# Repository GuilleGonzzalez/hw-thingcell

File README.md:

# ThingCell

## Description
'ThhingCell' is a device designed to control a other devices with a relay with MQTT over 4G .

Firmware used in this device is [fw-thingcell](https://github.com/GuilleGonzzalez/fw-thigcell), a custom made firmware implemented using [Arduino Home Assistant](https://github.com/dawidchyrzynski/arduino-home-assistant/tree/main) Arduino library ([docs](https://dawidchyrzynski.github.io/arduino-home-assistant/)).

## Power supply (WIP)

## Microprocessor (WIP)
Espressif [ESP8266](https://www.espressif.com/en/products/modules) module.

## Environmental sensing (WIP)
The board has enviromental sensors to measure temperature, humidity and atmospheric pressure:

### Temperature and humidity sensor
* Sensirion [SHT40](https://sensirion.com/products/catalog/SHT40).

### Pressure sensor
* Bosch [BMP581](https://www.bosch-sensortec.com/products/environmental-sensors/pressure-sensors/bmp581/).
  
## LEDs and buttons (WIP)

## Pin assignment (WIP)

| PIN     | Func    |
| ------- | ------- |
| GPIOx   | F1    |

## Enclosure (WIP)
* Custom made in [Fusion 360](https://www.autodesk.es/products/fusion-360/overview).

# Changelog (WIP)
All notable changes to this project will be documented in this section.

The format is based on [Keep a Changelog](https://keepachangelog.com/en/1.0.0/)

## [unreleased] - 2023-09-06
Unreleased

[Unreleased]: https://github.com/GuilleGonzzalez/hw-thingcell

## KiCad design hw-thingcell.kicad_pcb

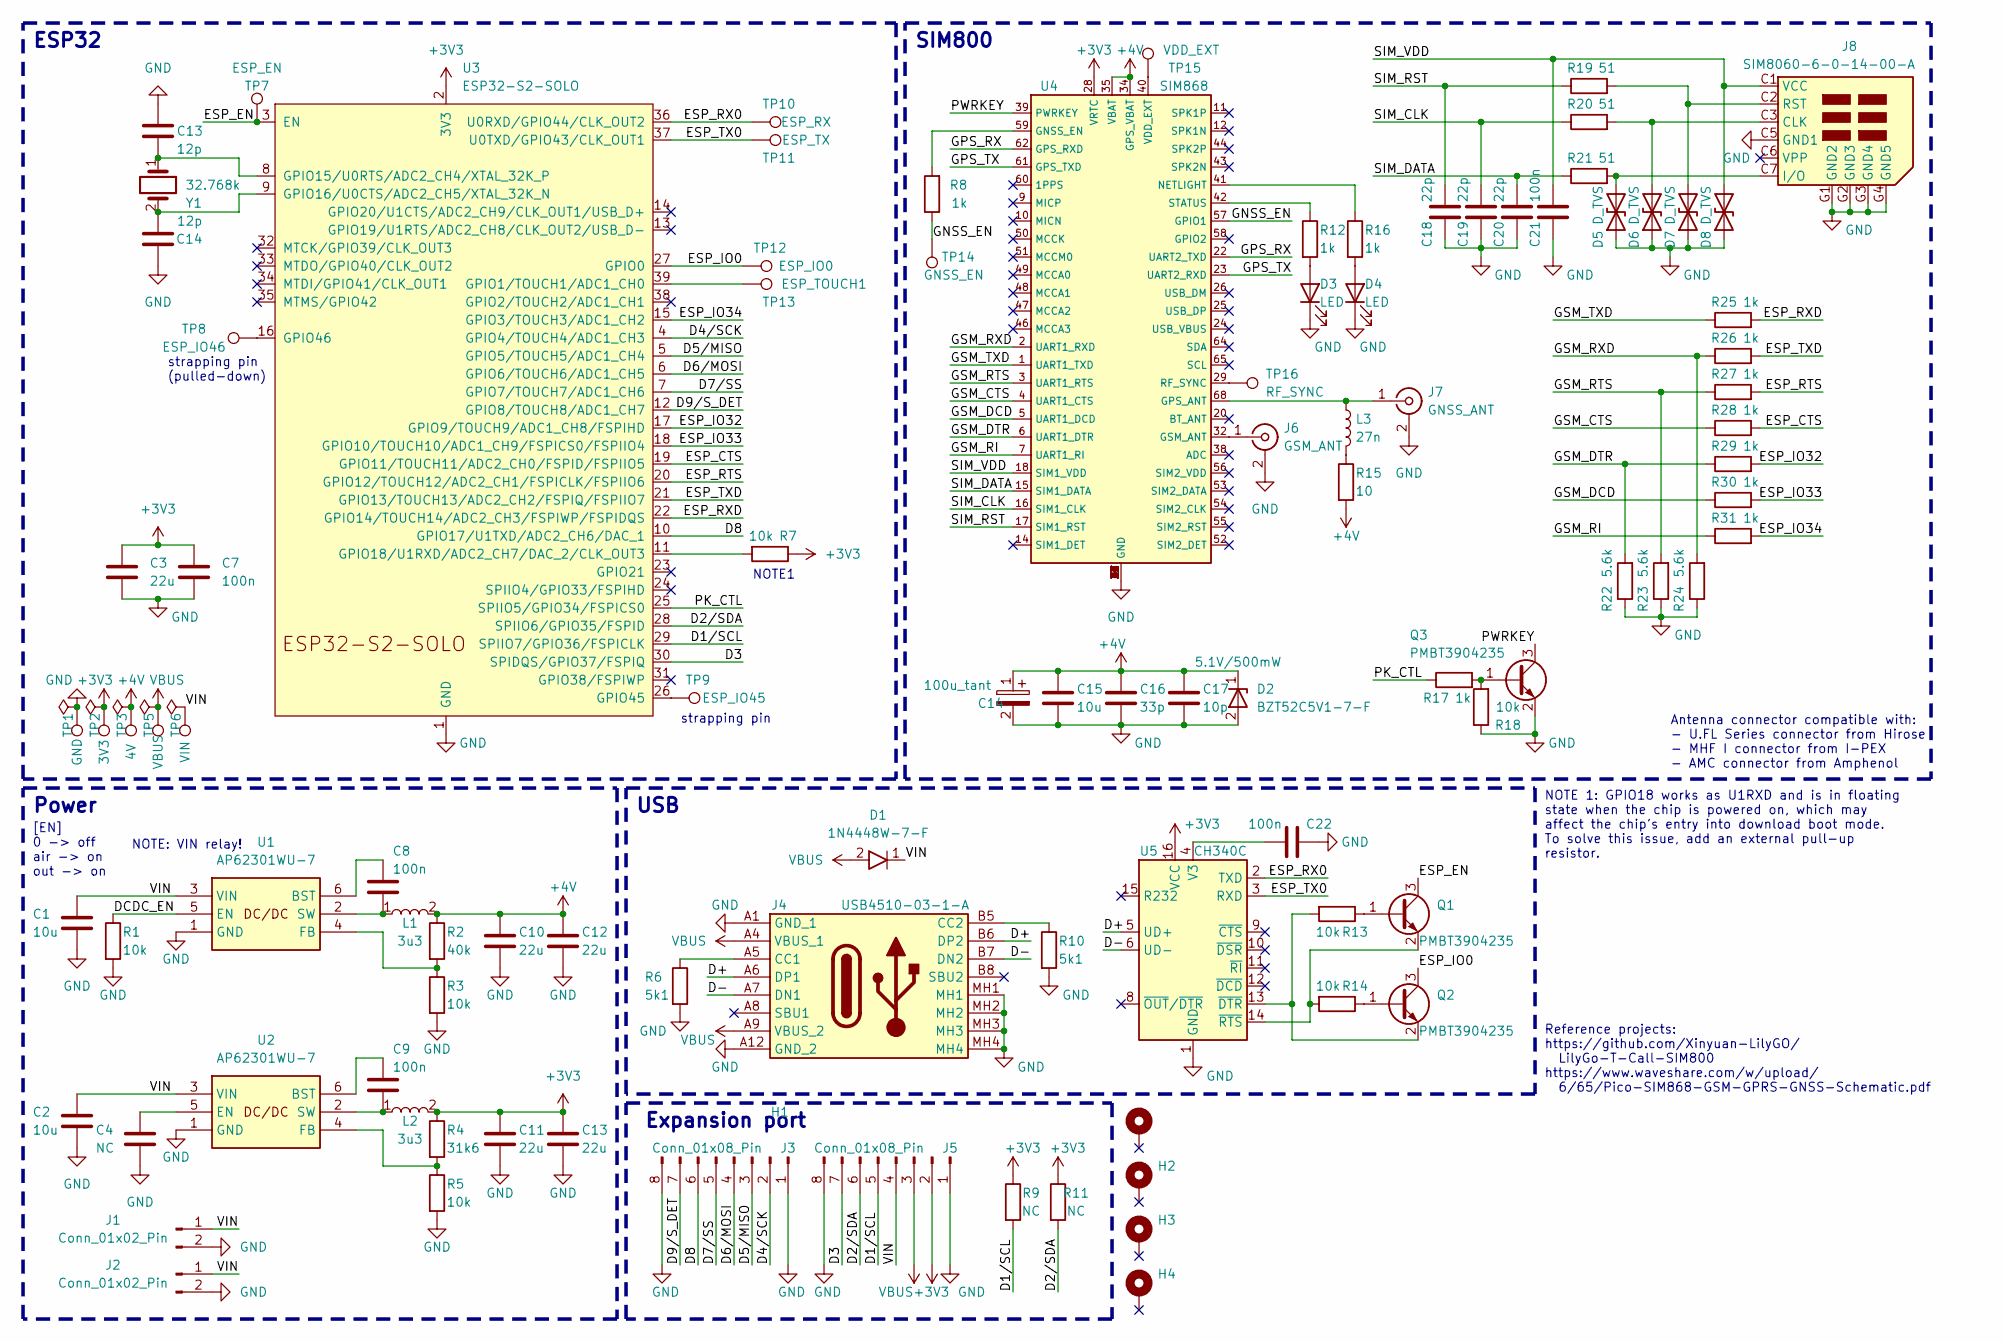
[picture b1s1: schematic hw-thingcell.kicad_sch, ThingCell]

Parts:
C1, C2, C15: 10u; C_0805_2012Metric
C3, C10, C11, C12, C13: 22u; C_0805_2012Metric
C4: NC; C_0402_1005Metric
C7, C8, C9, C21, C22: 100n; C_0402_1005Metric
C14: 100u_tant; CAPPM3528X210N; Manufacturer_Part_Number TPSB107K006R0250; Mouser Part Number 581-TPSB107K006R0250
C16: 33p; C_0402_1005Metric
C17: 10p; C_0402_1005Metric
C18, C19, C20: 22p; C_0402_1005Metric
D1: 1N4448W-7-F; D_SOD-123; Manufacturer_Part_Number 1N4448W-7-F; Mouser Part Number 621-1N4448W-F
D2: BZT52C5V1-7-F; SOD3716X145N; Manufacturer_Part_Number BZT52C5V1-7-F; Mouser Part Number 621-BZT52C5V1-F
D3, D4: LED; LED_0402_1005Metric
D5, D6, D7, D8: D_TVS; D_0402_1005Metric
H1, H2, H3, H4: MountingHole_Pad; MountingHole_2.2mm_M2_ISO7380_Pad
J1, J2: Conn_01x02_Pin; PinSocket_1x02_P2.54mm_Vertical
J3, J5: Conn_01x08_Pin; PinSocket_1x08_P2.54mm_Vertical
J4: USB4510-03-1-A; USB4510031A; Mouser Part Number 640-USB4510031A
J6: GSM_ANT; U.FL_CONNECTOR
J7: GNSS_ANT; U.FL_CONNECTOR
J8: SIM8060-6-0-14-00-A; SIM8060601400A; Manufacturer_Part_Number SIM8060-6-0-14-00-A; Mouser Part Number 640-SIM8060601400A
L1, L2: 3u3; SRN5020TA3R3M; Manufacturer_Part_Number SRN5020TA-3R3M; Mouser Part Number 652-SRN5020TA-3R3M
L3: 27n; L_0402_1005Metric
Q1, Q2, Q3: PMBT3904235; SOT-23; Manufacturer_PN PMBT3904,235
R1, R3, R5, R7, R13, R14, R18: 10k; R_0402_1005Metric
R2: 40k; R_0402_1005Metric
R4: 31k6; R_0402_1005Metric
R6, R10: 5k1; R_0402_1005Metric
R8, R12, R16, R17, R25, R26, R27, R28, R29, R30, R31: 1k; R_0402_1005Metric
R9, R11: NC; R_0402_1005Metric
R15: 10; R_0402_1005Metric
R19, R20, R21: 51; R_0402_1005Metric
R22, R23, R24: 5.6k; R_0402_1005Metric
TP1: GND; TestPoint_Pad_D1.0mm
TP2: 3V3; TestPoint_Pad_D1.0mm
TP3: 4V; TestPoint_Pad_D1.0mm
TP5: VBUS; TestPoint_Pad_D1.0mm
TP6: VIN; TestPoint_Pad_D1.0mm
TP7: ESP_EN; TestPoint_Pad_D1.0mm
TP8: ESP_IO46; TestPoint_Pad_D1.0mm
TP9: ESP_IO45; TestPoint_Pad_D1.0mm
TP10: ESP_RX; TestPoint_Pad_D1.0mm
TP11: ESP_TX; TestPoint_Pad_D1.0mm
TP12: ESP_IO0; TestPoint_Pad_D1.0mm
TP13: ESP_TOUCH1; TestPoint_Pad_D1.0mm
TP14: GNSS_EN; TestPoint_Pad_D1.0mm
TP15: VDD_EXT; TestPoint_Pad_D1.0mm
TP16: RF_SYNC; TestPoint_Pad_D1.0mm
U1, U2: AP62301WU-7; SOT95P280X100-6N; Manufacturer_Part_Number AP62301WU-7; Mouser Part Number 621-AP62301WU-7
U3: ESP32-S2-SOLO
U4: SIM868
U5: CH340C; SOIC-16_3.9x9.9mm_P1.27mm
Y1: 32.768k; SC32S7PF20PPM; Manufacturer_Part_Number SC32S-7PF20PPM; Mouser Part Number 628-SC32S-7PF20PPM

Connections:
/D1/SCL: J5.5, R9.2, U3.29 (SPIIO7/GPIO36/FSPICLK)
/D2/SDA: J5.6, R11.2, U3.28 (SPIIO6/GPIO35/FSPID)
/D3: J5.7, U3.30 (SPIDQS/GPIO37/FSPIQ)
/D4/SCK: J3.2, U3.4 (GPIO4/TOUCH4/ADC1_CH3)
/D5/MISO: J3.3, U3.5 (GPIO5/TOUCH5/ADC1_CH4)
/D6/MOSI: J3.4, U3.6 (GPIO6/TOUCH6/ADC1_CH5)
/D7/SS: J3.5, U3.7 (GPIO7/TOUCH7/ADC1_CH6)
/D8: J3.6, U3.10 (GPIO17/U1TXD/ADC2_CH6/DAC_1)
/D9/S_DET: J3.7, U3.12 (GPIO8/TOUCH8/ADC1_CH7)
/D+: J4.A6 (DP1), J4.B6 (DP2), U5.5 (UD+)
/D-: J4.A7 (DN1), J4.B7 (DN2), U5.6 (UD-)
/DCDC_EN: R1.1, U1.5 (EN)
/ESP_CTS: R28.2, U3.19 (GPIO11/TOUCH11/ADC2_CH0/FSPID/FSPIIO5)
/ESP_EN: Q1.3, TP7.1, U3.3 (EN)
/ESP_IO0: Q2.3, TP12.1, U3.27 (GPIO0)
/ESP_IO32: R29.2, U3.17 (GPIO9/TOUCH9/ADC1_CH8/FSPIHD)
/ESP_IO33: R30.2, U3.18 (GPIO10/TOUCH10/ADC1_CH9/FSPICS0/FSPIIO4)
/ESP_IO34: R31.2, U3.15 (GPIO3/TOUCH3/ADC1_CH2)
/ESP_RTS: R27.2, U3.20 (GPIO12/TOUCH12/ADC2_CH1/FSPICLK/FSPIIO6)
/ESP_RX0: TP10.1, U3.36 (U0RXD/GPIO44/CLK_OUT2), U5.2 (TXD)
/ESP_RXD: R25.2, U3.22 (GPIO14/TOUCH14/ADC2_CH3/FSPIWP/FSPIDQS)
/ESP_TX0: TP11.1, U3.37 (U0TXD/GPIO43/CLK_OUT1), U5.3 (RXD)
/ESP_TXD: R26.2, U3.21 (GPIO13/TOUCH13/ADC2_CH2/FSPIQ/FSPIIO7)
/GNSS_EN: R8.1, TP14.1, U4.57 (GPIO1)
/GPS_RX: U4.22 (UART2_TXD), U4.62 (GPS_RXD)
/GPS_TX: U4.23 (UART2_RXD), U4.61 (GPS_TXD)
/GSM_CTS: R28.1, U4.4 (UART1_CTS)
/GSM_DCD: R30.1, U4.5 (UART1_DCD)
/GSM_DTR: R22.2, R29.1, U4.6 (UART1_DTR)
/GSM_RI: R31.1, U4.7 (UART1_RI)
/GSM_RTS: R23.2, R27.1, U4.3 (UART1_RTS)
/GSM_RXD: R24.2, R26.1, U4.2 (UART1_RXD)
/GSM_TXD: R25.1, U4.1 (UART1_TXD)
/PK_CTL: R17.1, U3.25 (SPIIO5/GPIO34/FSPICS0)
/PWRKEY: Q3.3, U4.39 (PWRKEY)
/SIM_CLK: C19.1, R20.1, U4.16 (SIM1_CLK)
/SIM_DATA: C20.1, R21.1, U4.15 (SIM1_DATA)
/SIM_RST: C18.1, R19.1, U4.17 (SIM1_RST)
/SIM_VDD: C21.1, D8.2 (A2), J8.C1 (VCC), U4.18 (SIM1_VDD)
/VIN: C1.1, C2.1, D1.1, J1.1, J2.1, J5.4, TP6.1, U1.3 (VIN), U2.3 (VIN)
unnamed: D3.2 (A), R12.2
unnamed: D4.2 (A), R16.2
unnamed: D5.2 (A2), J8.C7 (I/O), R21.2
unnamed: D6.2 (A2), J8.C3 (CLK), R20.2
unnamed: D7.2 (A2), J8.C2 (RST), R19.2
unnamed: J4.A5 (CC1), R6.1
unnamed: J4.B5 (CC2), R10.1
unnamed: J6.1 (In), U4.32 (GSM_ANT)
unnamed: J7.1 (In), L3.1, U4.68 (GPS_ANT)
unnamed: L3.2, R15.1
unnamed: Q1.1, R13.1
unnamed: Q2.1, R14.1
unnamed: Q3.1, R17.2, R18.2
unnamed: C8.1, U1.6 (BST)
unnamed: R2.2, R3.1, U1.4 (FB)
unnamed: C8.2, L1.1, U1.2 (SW)
unnamed: C9.1, U2.6 (BST)
unnamed: C4.1, U2.5 (EN)
unnamed: R4.2, R5.1, U2.4 (FB)
unnamed: C9.2, L2.1, U2.2 (SW)
unnamed: TP13.1, U3.39 (GPIO1/TOUCH1/ADC1_CH0)
unnamed: R7.2, U3.11 (GPIO18/U1RXD/ADC2_CH7/DAC_2/CLK_OUT3)
unnamed: TP9.1, U3.26 (GPIO45)
unnamed: TP8.1, U3.16 (GPIO46)
unnamed: R8.2, U4.59 (GNSS_EN)
unnamed: R16.1, U4.41 (NETLIGHT)
unnamed: TP16.1, U4.29 (RF_SYNC)
unnamed: R12.1, U4.42 (STATUS)
unnamed: TP15.1, U4.40 (VDD_EXT)
unnamed: C22.1, U5.4 (V3)
unnamed: Q2.2, R13.2, U5.13 (~DTR)
unnamed: Q1.2, R14.2, U5.14 (~RTS)
VBUS: D1.2, J4.A4 (VBUS_1), J4.A9 (VBUS_2), J5.3, TP5.1

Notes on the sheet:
NOTE 1: GPIO18 works as U1RXD and is in floating state when the chip is powered on, which may affect the chip’s entry into download boot mode. To solve this issue, add an external pull-up resistor.
NOTE1
strapping pin (pulled-down)
strapping pin
Antenna connector compatible with: - U.FL Series connector from Hirose - MHF I connector from I-PEX - AMC connector from Amphenol
ESP32
[EN] 0 -> off air -> on out -> on
Reference projects: https://github.com/Xinyuan-LilyGO/ LilyGo-T-Call-SIM800 https://www.waveshare.com/w/upload/ 6/65/Pico-SIM868-GSM-GPRS-GNSS-Schematic.pdf
NOTE: VIN relay!
Expansion port
SIM800
Power
USB

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
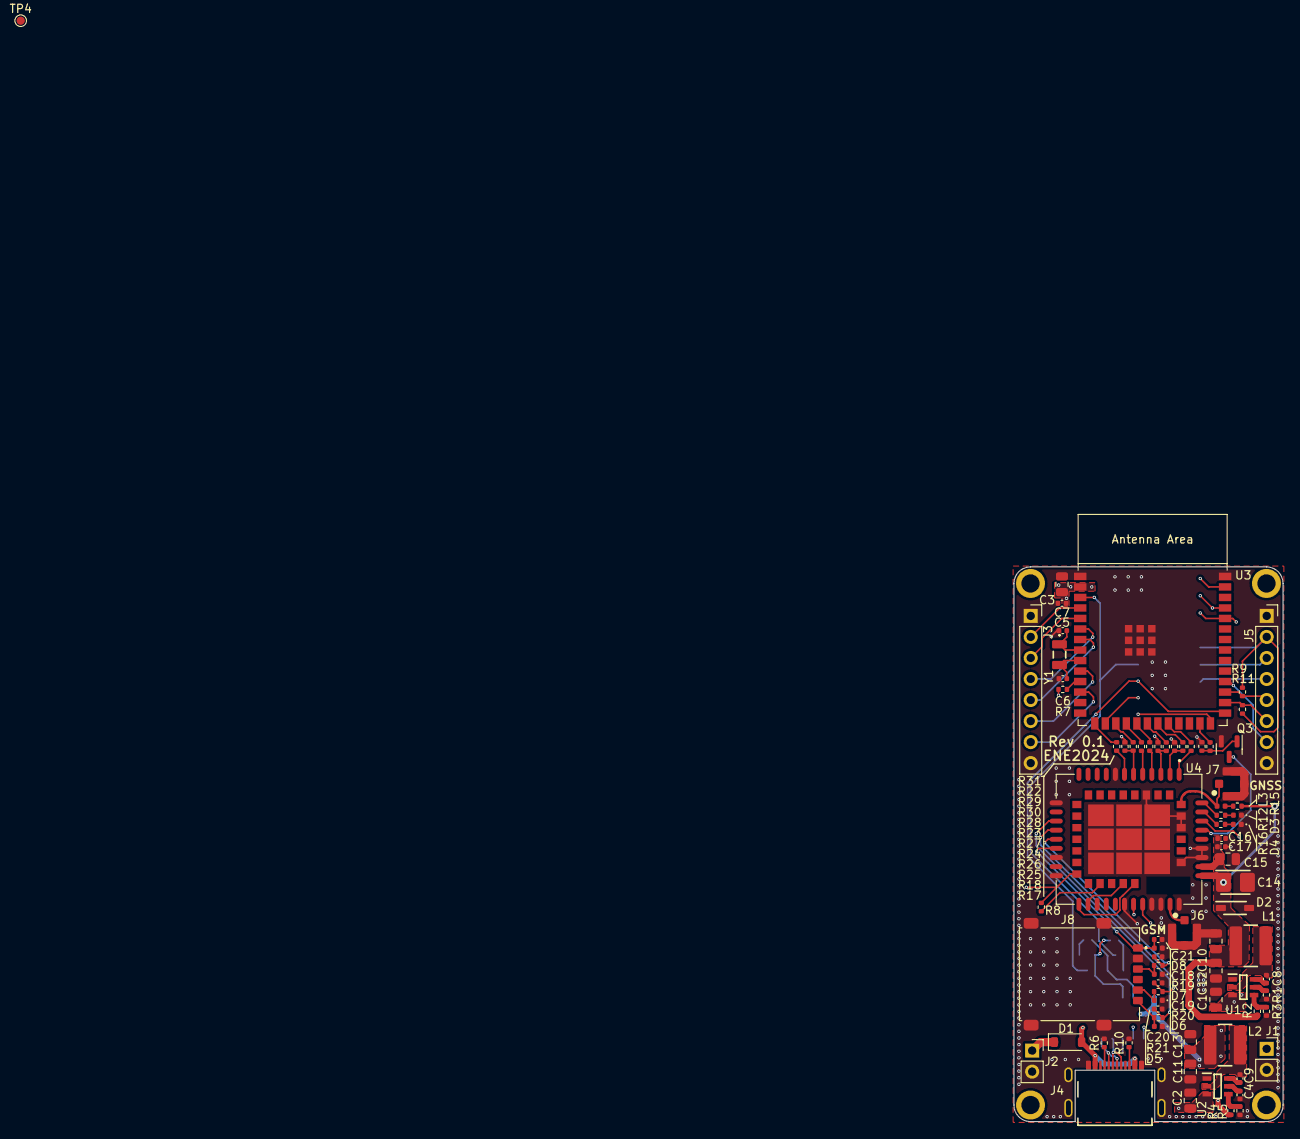
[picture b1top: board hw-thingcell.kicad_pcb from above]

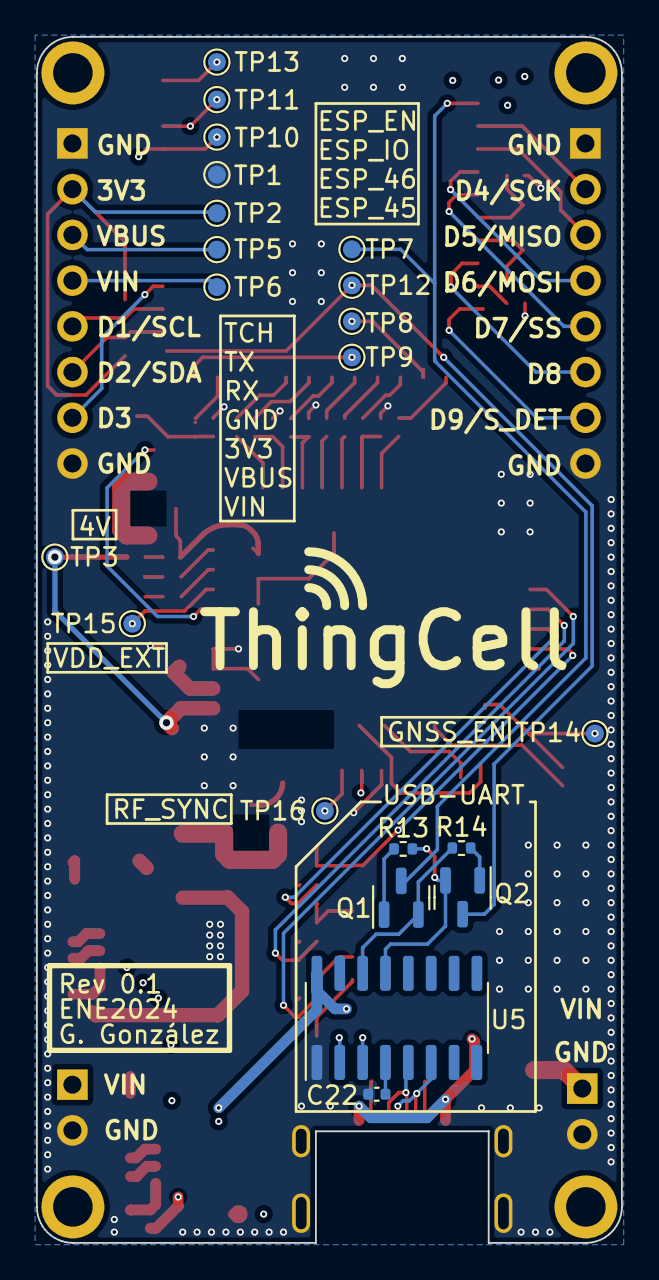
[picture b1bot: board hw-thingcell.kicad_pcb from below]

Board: 4 copper layers, 32.5 x 67.0 mm, 101 parts (21 on the bottom side), 78 nets.

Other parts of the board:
C5, C6: 12p; C_0402_1005Metric
TP4: 5V; TestPoint_Pad_D1.0mm

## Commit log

2023-09-06 Draft schematic
2023-09-15 Continue with schematic adding ESP and SIM components
2023-11-23 Work on schematic
2023-11-23 Replace SIM800C with SIM868
2023-11-24 Add antenna connector and passive components
2023-11-24 Add USB-UART and USB-C connector
2023-11-25 Change ESP-WROOM to SOLO and schematic relocation
2023-12-01 Add supply diode and match all symbols&footprints
2023-12-05 Sch reviewed
2023-12-05 First placement
2024-01-08 Routed all components
2024-01-08 Work in texts and graphics
2024-01-09 Add coplanar wave guides
2024-01-23 Final revision
2024-01-23 Update Gerber export config
